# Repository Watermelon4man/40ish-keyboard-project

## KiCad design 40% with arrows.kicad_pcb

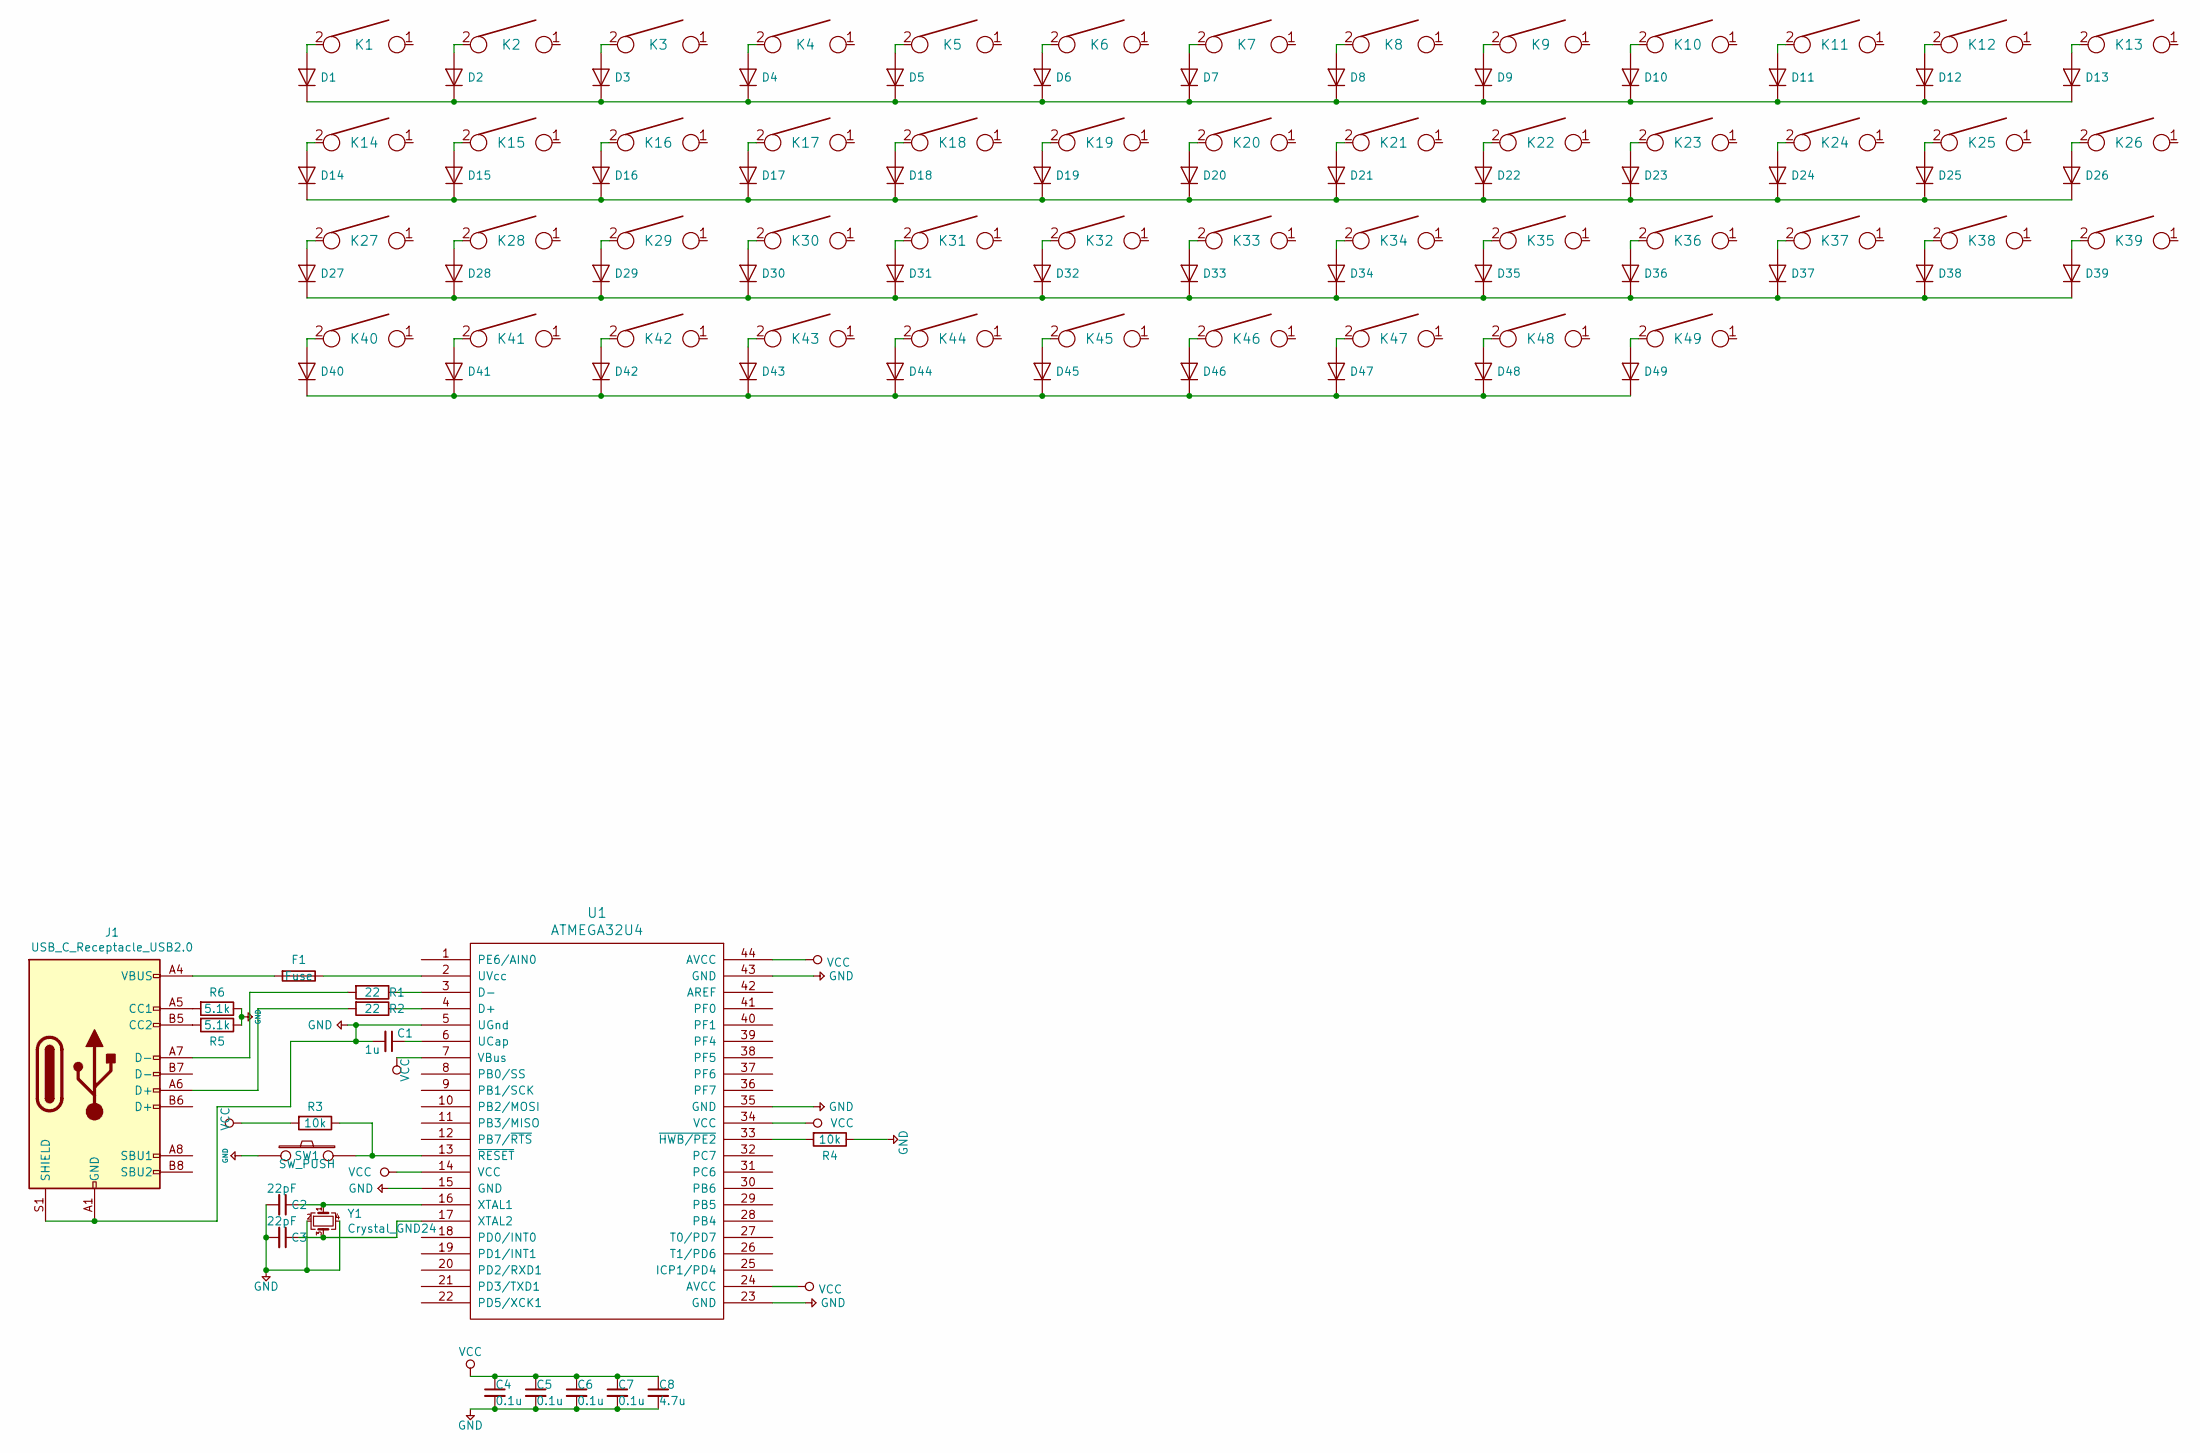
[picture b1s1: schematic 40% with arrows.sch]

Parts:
C1: 1u; C_0402_1005Metric
C2, C3: 22pF; C_0402_1005Metric
C4, C5, C6, C7: 0.1u; C_0402_1005Metric
C8: 4.7u; C_0402_1005Metric
D1, D2, D3, D4, D5, D6, D7, D8, D9, D10, D11, D12, D13, D14, D15, D16, D17, D18, D19, D20, D21, D22, D23, D24, D25, D26, D27, D28, D29, D30, D31, D32, D33, D34, D35, D36, D37, D38, D39, D40, D41, D42, D43, D44, D45, D46, D47, D48, D49: D; D_SOD123
F1: Fuse; Fuse_0603_1608Metric
J1: USB_C_Receptacle_USB2.0; USB_C_Receptacle_Palconn_UTC16-G
K1, K2, K3, K4, K5, K6, K7, K8, K9, K10, K11, K12, K15, K16, K17, K18, K19, K20, K21, K22, K23, K24, K25, K28, K29, K30, K31, K32, K33, K34, K35, K36, K37, K38, K39, K45, K46, K47, K48, K49: KEYSW; MXOnly-1U-NoLED
K13, K27: KEYSW; MXOnly-1.75U-NoLED
K14, K40, K41, K42: KEYSW; MXOnly-1.25U-NoLED
K26: KEYSW; MXOnly-1.5U-NoLED
K43: KEYSW; MXOnly-2.25U-ReversedStabilizers-NoLED
K44: KEYSW; MXOnly-2.75U-ReversedStabilizers-NoLED
R1, R2: 22; R_0402_1005Metric
R3, R4: 10k; R_0402_1005Metric
R5, R6: 5.1k; R_0402_1005Metric
SW1: SW_PUSH; SKQG-1155865
U1: ATMEGA32U4; TQFP-44_10x10mm_Pitch0.8mm
Y1: Crystal_GND24; Crystal_SMD_SeikoEpson_FA238-4Pin_3.2x2.5mm

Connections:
+5V: C1.2, C2.2, C3.2, C4.2, C5.2, C6.2, C7.2, C8.2, J1.A1 (GND), J1.A12 (GND), J1.B1 (GND), J1.B12 (GND), J1.S1 (SHIELD), R4.1, R5.1, R6.1, SW1.1, U1.5 (UGnd), U1.15 (GND), U1.23 (GND), U1.35 (GND), U1.43 (GND), Y1.2, Y1.4
unnamed: C1.1, U1.6 (UCap)
unnamed: C2.1, U1.16 (XTAL1), Y1.1
unnamed: C3.1, U1.17 (XTAL2), Y1.3
unnamed: D1.1 (K), D2.1 (K), D3.1 (K), D4.1 (K), D5.1 (K), D6.1 (K), D7.1 (K), D8.1 (K), D9.1 (K), D10.1 (K), D11.1 (K), D12.1 (K), D13.1 (K)
unnamed: D1.2 (A), K1.2
unnamed: D2.2 (A), K2.2
unnamed: D3.2 (A), K3.2
unnamed: D4.2 (A), K4.2
unnamed: D5.2 (A), K5.2
unnamed: D6.2 (A), K6.2
unnamed: D7.2 (A), K7.2
unnamed: D8.2 (A), K8.2
unnamed: D9.2 (A), K9.2
unnamed: D10.2 (A), K10.2
unnamed: D11.2 (A), K11.2
unnamed: D12.2 (A), K12.2
unnamed: D13.2 (A), K13.2
unnamed: D14.1 (K), D15.1 (K), D16.1 (K), D17.1 (K), D18.1 (K), D19.1 (K), D20.1 (K), D21.1 (K), D22.1 (K), D23.1 (K), D24.1 (K), D25.1 (K), D26.1 (K)
unnamed: D14.2 (A), K14.2
unnamed: D15.2 (A), K15.2
unnamed: D16.2 (A), K16.2
unnamed: D17.2 (A), K17.2
unnamed: D18.2 (A), K18.2
unnamed: D19.2 (A), K19.2
unnamed: D20.2 (A), K20.2
unnamed: D21.2 (A), K21.2
unnamed: D22.2 (A), K22.2
unnamed: D23.2 (A), K23.2
unnamed: D24.2 (A), K24.2
unnamed: D25.2 (A), K25.2
unnamed: D26.2 (A), K26.2
unnamed: D27.1 (K), D28.1 (K), D29.1 (K), D30.1 (K), D31.1 (K), D32.1 (K), D33.1 (K), D34.1 (K), D35.1 (K), D36.1 (K), D37.1 (K), D38.1 (K), D39.1 (K)
unnamed: D27.2 (A), K27.2
unnamed: D28.2 (A), K28.2
unnamed: D29.2 (A), K29.2
unnamed: D30.2 (A), K30.2
unnamed: D31.2 (A), K31.2
unnamed: D32.2 (A), K32.2
unnamed: D33.2 (A), K33.2
unnamed: D34.2 (A), K34.2
unnamed: D35.2 (A), K35.2
unnamed: D36.2 (A), K36.2
unnamed: D37.2 (A), K37.2
unnamed: D38.2 (A), K38.2
unnamed: D39.2 (A), K39.2
unnamed: D40.1 (K), D41.1 (K), D42.1 (K), D43.1 (K), D44.1 (K), D45.1 (K), D46.1 (K), D47.1 (K), D48.1 (K), D49.1 (K)
unnamed: D40.2 (A), K40.2
unnamed: D41.2 (A), K41.2
unnamed: D42.2 (A), K42.2
unnamed: D43.2 (A), K43.2
unnamed: D44.2 (A), K44.2
unnamed: D45.2 (A), K45.2
unnamed: D46.2 (A), K46.2
unnamed: D47.2 (A), K47.2
unnamed: D48.2 (A), K48.2
unnamed: D49.2 (A), K49.2
unnamed: F1.1, U1.2 (UVcc)
unnamed: F1.2, J1.A4 (VBUS), J1.A9 (VBUS), J1.B4 (VBUS), J1.B9 (VBUS)
unnamed: J1.A5 (CC1), R6.2
unnamed: J1.A6 (D+), R2.2
unnamed: J1.A7 (D-), R1.2
unnamed: J1.B5 (CC2), R5.2
unnamed: K7.1, U1.25 (ICP1/PD4)
unnamed: K8.1, U1.26 (T1/PD6)
unnamed: K9.1, U1.27 (T0/PD7)
unnamed: K10.1, U1.28 (PB4)
unnamed: K11.1, U1.29 (PB5)
unnamed: K12.1, U1.30 (PB6)
unnamed: K13.1, U1.31 (PC6)
unnamed: R1.1, U1.3 (D-)
unnamed: R2.1, U1.4 (D+)
unnamed: R3.1, SW1.2, U1.13 (~RESET)
unnamed: R4.2, U1.33 (~HWB/PE2)
VCC: C4.1, C5.1, C6.1, C7.1, C8.1, R3.2, U1.7 (VBus), U1.14 (VCC), U1.24 (AVCC), U1.34 (VCC), U1.44 (AVCC)

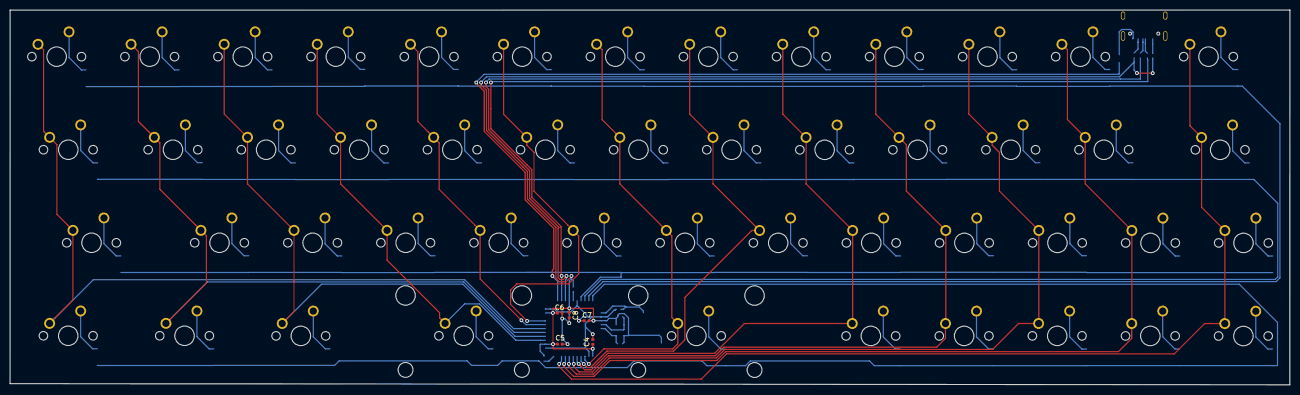
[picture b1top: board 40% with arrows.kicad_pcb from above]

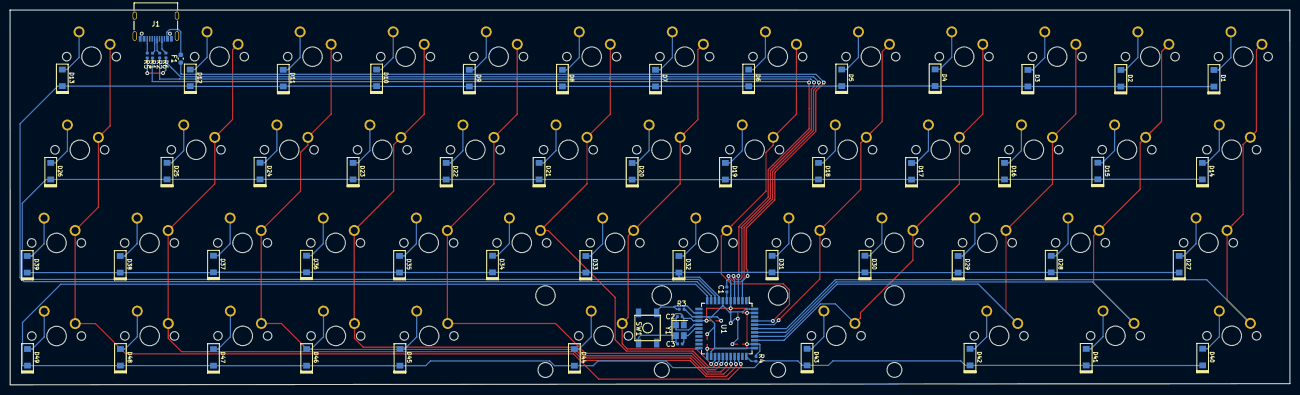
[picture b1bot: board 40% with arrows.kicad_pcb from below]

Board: 2 copper layers, 262.0 x 76.7 mm, 117 parts (63 on the bottom side), 75 nets.

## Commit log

2020-05-17 Changes to the pcb and schematic
    Changes to the pcb and schematic by the advice of Taylor.
2020-05-19 adder gerber
2020-06-18 changed some file directory's
2020-06-30 new thinges
2020-07-24 Update fp-info-cache
